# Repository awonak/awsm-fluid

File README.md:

# AWSM - Fluid

> [!NOTE]  
> This project is a work in progress and may contain errors.

3u 12hp Arduino based multi-purpose utility module. 

## Features

**Digital Inputs**

* 2 digital gate/trig inputs
* 2 buttons

**Analog Inputs**

* 4 slide potentiometers w/ addressable LEDs
* 4 CV inputs (-5v to 5v) w/ attenuator pots, summed with each slide pot.

**Analog Outputs**

* 2 PWM 0-10v outputs w/ LED indicator
* Each output paired with additional output which can be an inverted copy (-10v to 0v) or bipolar output (-10v to 10v).

## Concept

This module is meant to be a platform for creating unique utility module scripts using the given inputs and outputs. Some firmware examples are:

* CV controlable ADSR with gate / retrig inputs, envelope curves selected via button, envelope output with EOR/EOF output trigger.
* Clocked burst generator with high gate output during burst sequence.
* Dual LFO w/ shape and rate.
* Random cv generator w/ envelopes.

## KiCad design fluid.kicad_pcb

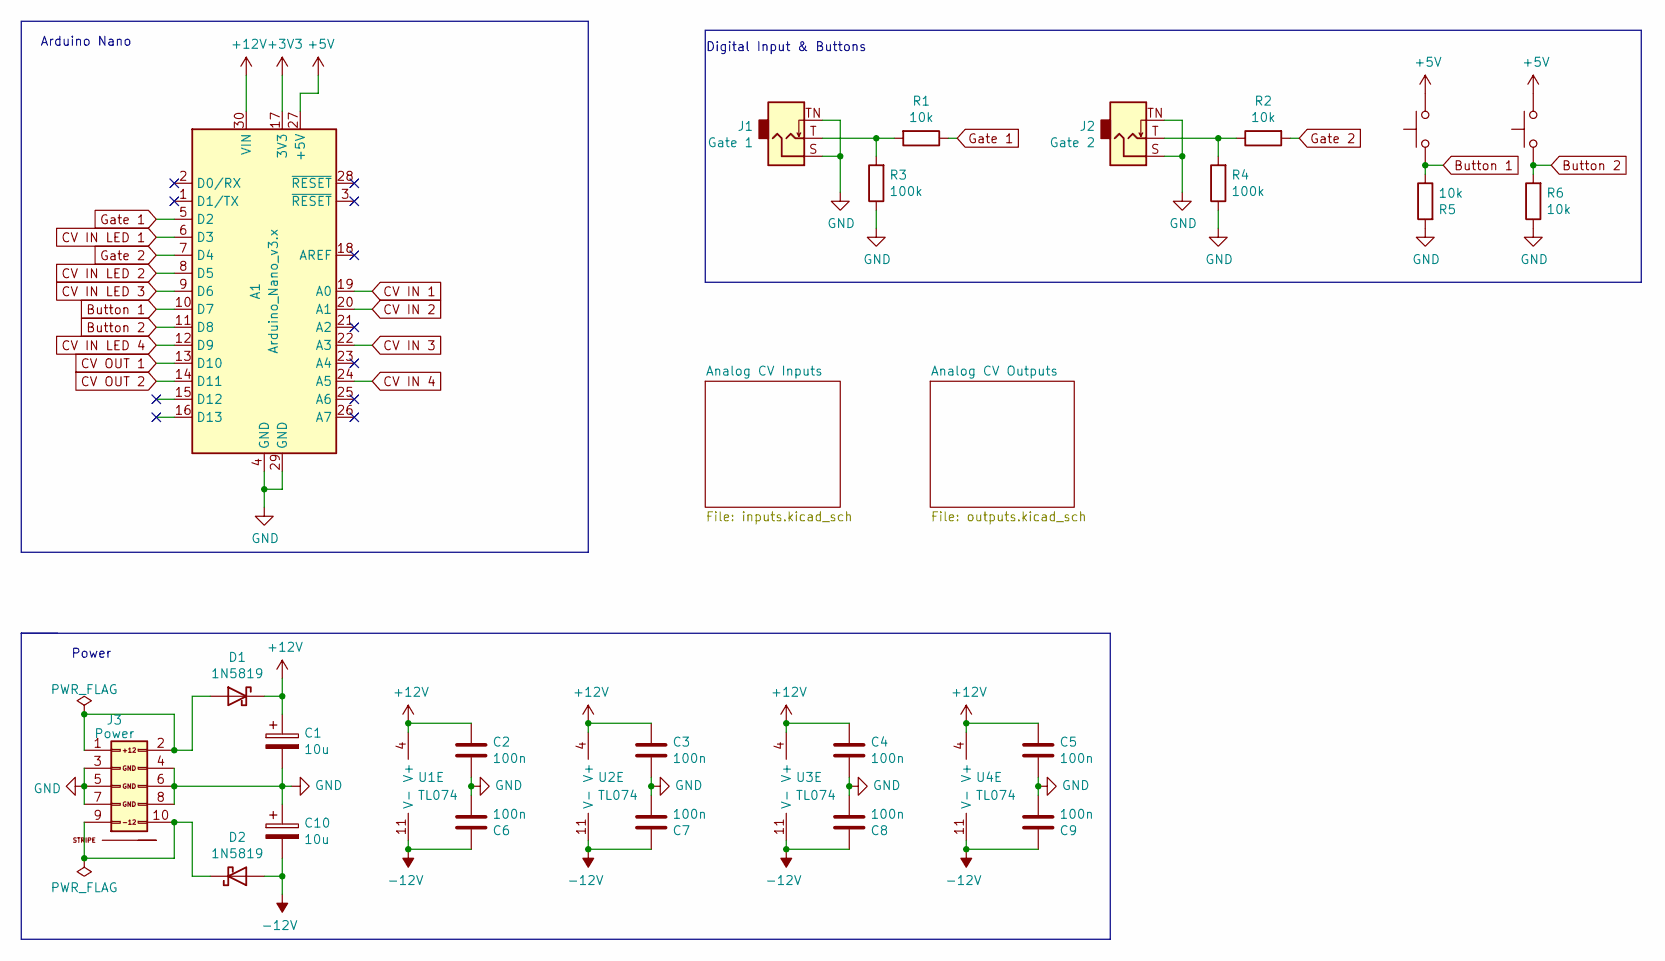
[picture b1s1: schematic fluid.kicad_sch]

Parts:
A1: Arduino_Nano_v3.x; Arduino_Nano
C1, C10: 10u; CP_EIA-3216-18_Kemet-A; LCSC C7171
C2, C3, C4, C5, C6, C7, C8, C9: 100n; C_0402_1005Metric; LCSC C1525
D1, D2: 1N5819; D_SOD-323; LCSC C191023
J1: Gate 1; Jack_3.5mm_QingPu_WQP-PJ398SM_Vertical_CircularHoles_3dModel
J2: Gate 2; Jack_3.5mm_QingPu_WQP-PJ398SM_Vertical_CircularHoles_3dModel
J3: Power; Pins_2x05_2.54mm_TH_EurorackPower
R1, R2, R5, R6: 10k; R_0402_1005Metric; LCSC C25744
R3, R4: 100k; R_0402_1005Metric; LCSC C25741
SW1, SW2: Button; SW_PUSH_6mm
U1, U2, U3, U4: TL074; SOIC-14_3.9x8.7mm_P1.27mm; LCSC C6963

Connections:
+3V3: A1.17 (3V3)
+5V: A1.27 (+5V), SW1.2, SW2.2; also elsewhere on the board
+12V: A1.30 (VIN), C1.1, C2.2, C3.2, C4.2, C5.2, D1.1 (K), U1.4 (V+), U2.4 (V+), U3.4 (V+), U4.4 (V+)
-12V: C6.2, C7.2, C8.2, C9.2, C10.2, D2.2 (A), U1.11 (V-), U2.11 (V-), U3.11 (V-), U4.11 (V-)
Button 1: A1.10 (D7), R5.1, SW1.1
Button 2: A1.11 (D8), R6.2, SW2.1
CV IN 1: A1.19 (A0); also elsewhere on the board
CV IN 2: A1.20 (A1); also elsewhere on the board
CV IN 3: A1.22 (A3); also elsewhere on the board
CV IN 4: A1.24 (A5); also elsewhere on the board
CV IN LED 1: A1.6 (D3); also elsewhere on the board
CV IN LED 2: A1.8 (D5); also elsewhere on the board
CV IN LED 3: A1.9 (D6); also elsewhere on the board
CV IN LED 4: A1.12 (D9); also elsewhere on the board
CV OUT 1: A1.13 (D10); also elsewhere on the board
CV OUT 2: A1.14 (D11); also elsewhere on the board
GND: A1.4 (GND), A1.29 (GND), C1.2, C2.1, C3.1, C4.1, C5.1, C6.1, C7.1, C8.1, C9.1, C10.1, J1.S, J1.TN, J2.S, J2.TN, J3.3 (GND), J3.4 (GND), J3.5 (GND), J3.6 (GND), J3.7 (GND), J3.8 (GND), R3.1, R4.1, R5.2, R6.1; also elsewhere on the board
Gate 1: A1.5 (D2), R1.1
Gate 2: A1.7 (D4), R2.2
unnamed: D1.2 (A), J3.1 (+12V), J3.2 (+12V)
unnamed: D2.1 (K), J3.9 (-12V), J3.10 (-12V)
unnamed: J1.T, R1.2, R3.2
unnamed: J2.T, R2.1, R4.2

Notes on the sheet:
Arduino Nano
Power
Digital Input & Buttons

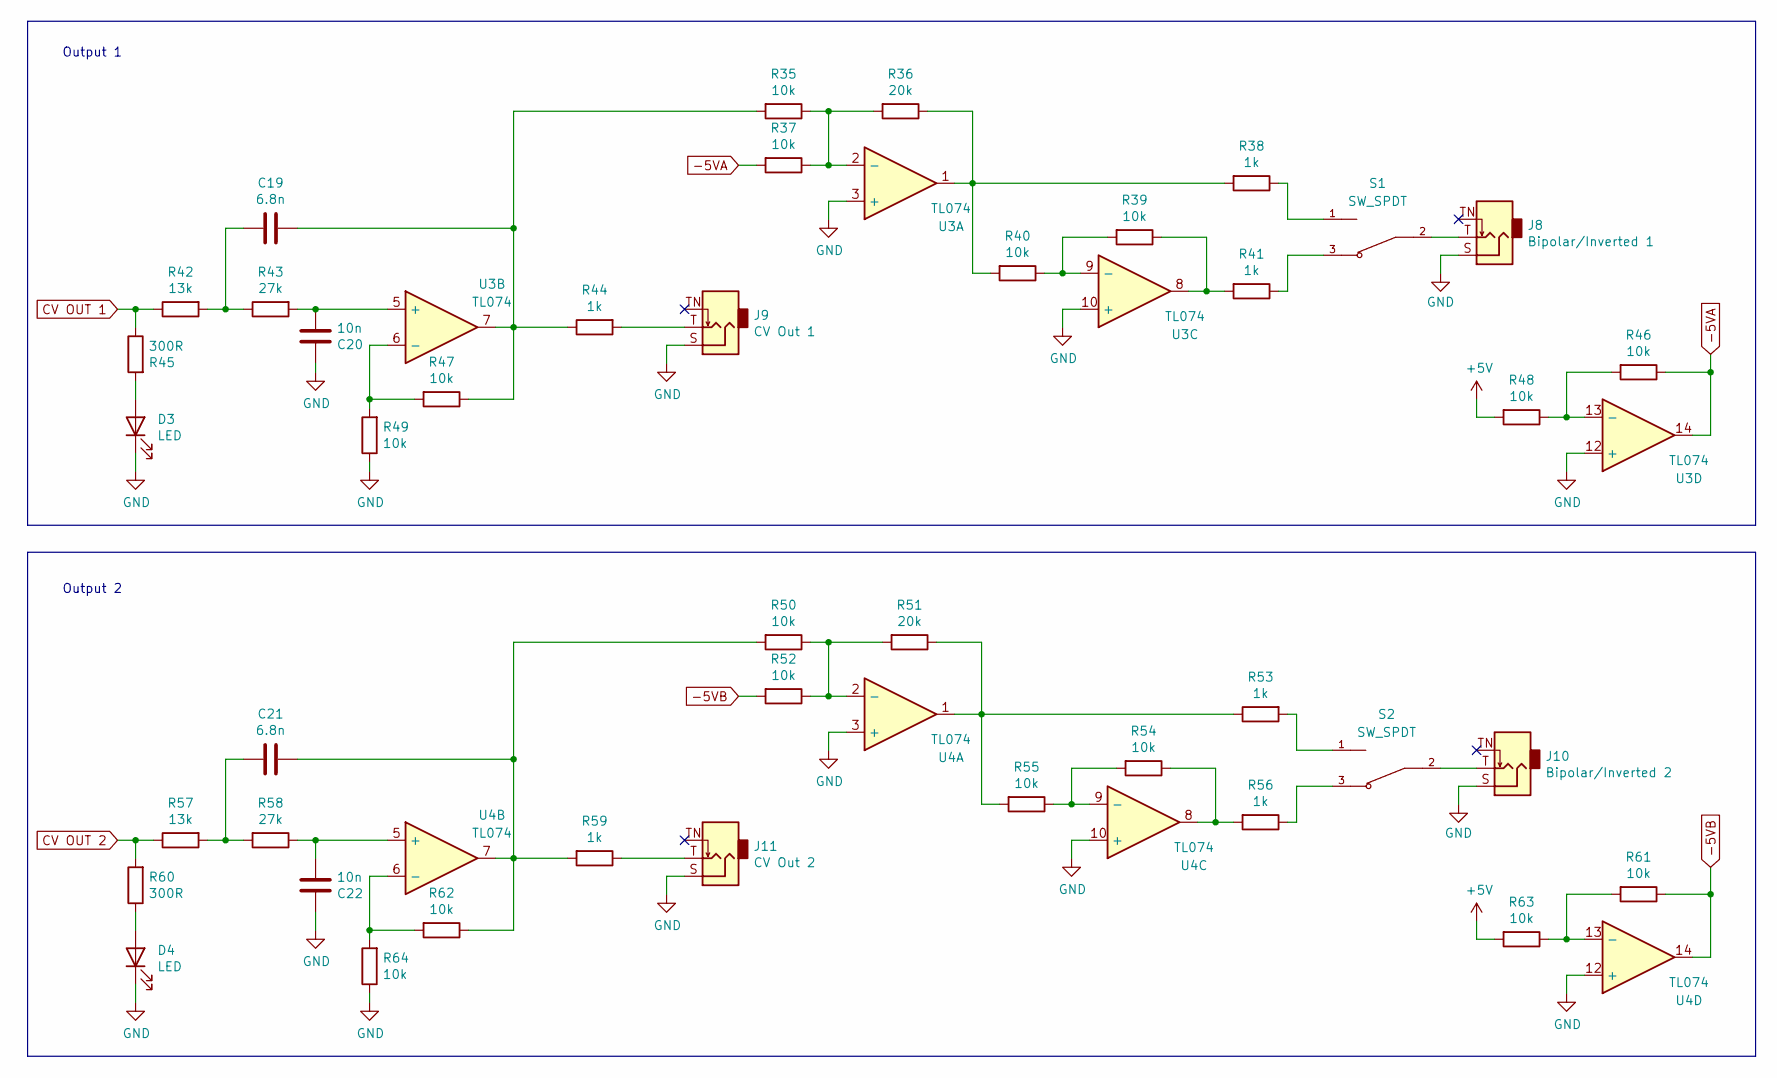
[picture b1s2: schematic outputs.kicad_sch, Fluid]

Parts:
C19, C21: 6.8n; C_0402_1005Metric; LCSC C1542
C20, C22: 10n; C_0402_1005Metric; LCSC C15195
D3, D4: LED; LED_D3.0mm
J8: Bipolar/Inverted 1; Jack_3.5mm_QingPu_WQP-PJ398SM_Vertical_CircularHoles_3dModel
J9: CV Out 1; Jack_3.5mm_QingPu_WQP-PJ398SM_Vertical_CircularHoles_3dModel
J10: Bipolar/Inverted 2; Jack_3.5mm_QingPu_WQP-PJ398SM_Vertical_CircularHoles_3dModel
J11: CV Out 2; Jack_3.5mm_QingPu_WQP-PJ398SM_Vertical_CircularHoles_3dModel
R35, R37, R39, R40, R46, R47, R48, R49, R50, R52, R54, R55, R61, R62, R63, R64: 10k; R_0402_1005Metric; LCSC C25744
R36, R51: 20k; R_0402_1005Metric; LCSC C25765
R38, R41, R44, R53, R56, R59: 1k; R_0402_1005Metric; LCSC C11702
R42, R57: 13k; R_0603_1608Metric; LCSC C22797
R43, R58: 27k; R_0402_1005Metric; LCSC C25771
R45, R60: 300R; R_0402_1005Metric; LCSC C25102
S1, S2: SW_SPDT; SW_2MS1T1B1M2QES
U3, U4: TL074; SOIC-14_3.9x8.7mm_P1.27mm; LCSC C6963

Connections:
+5V: R48.2, R63.2; also elsewhere on the board
-5VA: R37.2, R46.1, U3.14
-5VB: R52.2, R61.1, U4.14
CV OUT 1: R42.1, R45.1; also elsewhere on the board
CV OUT 2: R57.1, R60.2; also elsewhere on the board
GND: C20.2, C22.2, D3.1 (K), D4.1 (K), J8.S, J9.S, J10.S, J11.S, R49.1, R64.1, U3.3 (+), U3.10 (+), U3.12 (+), U4.3 (+), U4.10 (+), U4.12 (+); also elsewhere on the board
unnamed: C19.1, R35.2, R44.1, R47.1, U3.7
unnamed: C19.2, R42.2, R43.1
unnamed: C21.1, R50.2, R59.2, R62.1, U4.7
unnamed: C21.2, R57.2, R58.2
unnamed: D3.2 (A), R45.2
unnamed: D4.2 (A), R60.1
unnamed: J8.T, S1.2
unnamed: J9.T, R44.2
unnamed: J10.T, S2.2
unnamed: J11.T, R59.1
unnamed: R36.1, R38.2, R40.2, U3.1
unnamed: R38.1, S1.1
unnamed: R39.1, R41.2, U3.8
unnamed: R41.1, S1.3
unnamed: R51.1, R53.1, R55.2, U4.1
unnamed: R53.2, S2.1
unnamed: R54.1, R56.2, U4.8
unnamed: R56.1, S2.3
unnamed: R35.1, R36.2, R37.1, U3.2 (-)
unnamed: C20.1, R43.2, U3.5 (+)
unnamed: R47.2, R49.2, U3.6 (-)
unnamed: R39.2, R40.1, U3.9 (-)
unnamed: R46.2, R48.1, U3.13 (-)
unnamed: R50.1, R51.2, R52.1, U4.2 (-)
unnamed: C22.1, R58.1, U4.5 (+)
unnamed: R62.2, R64.2, U4.6 (-)
unnamed: R54.2, R55.1, U4.9 (-)
unnamed: R61.2, R63.1, U4.13 (-)

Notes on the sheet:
Output 2
Output 1

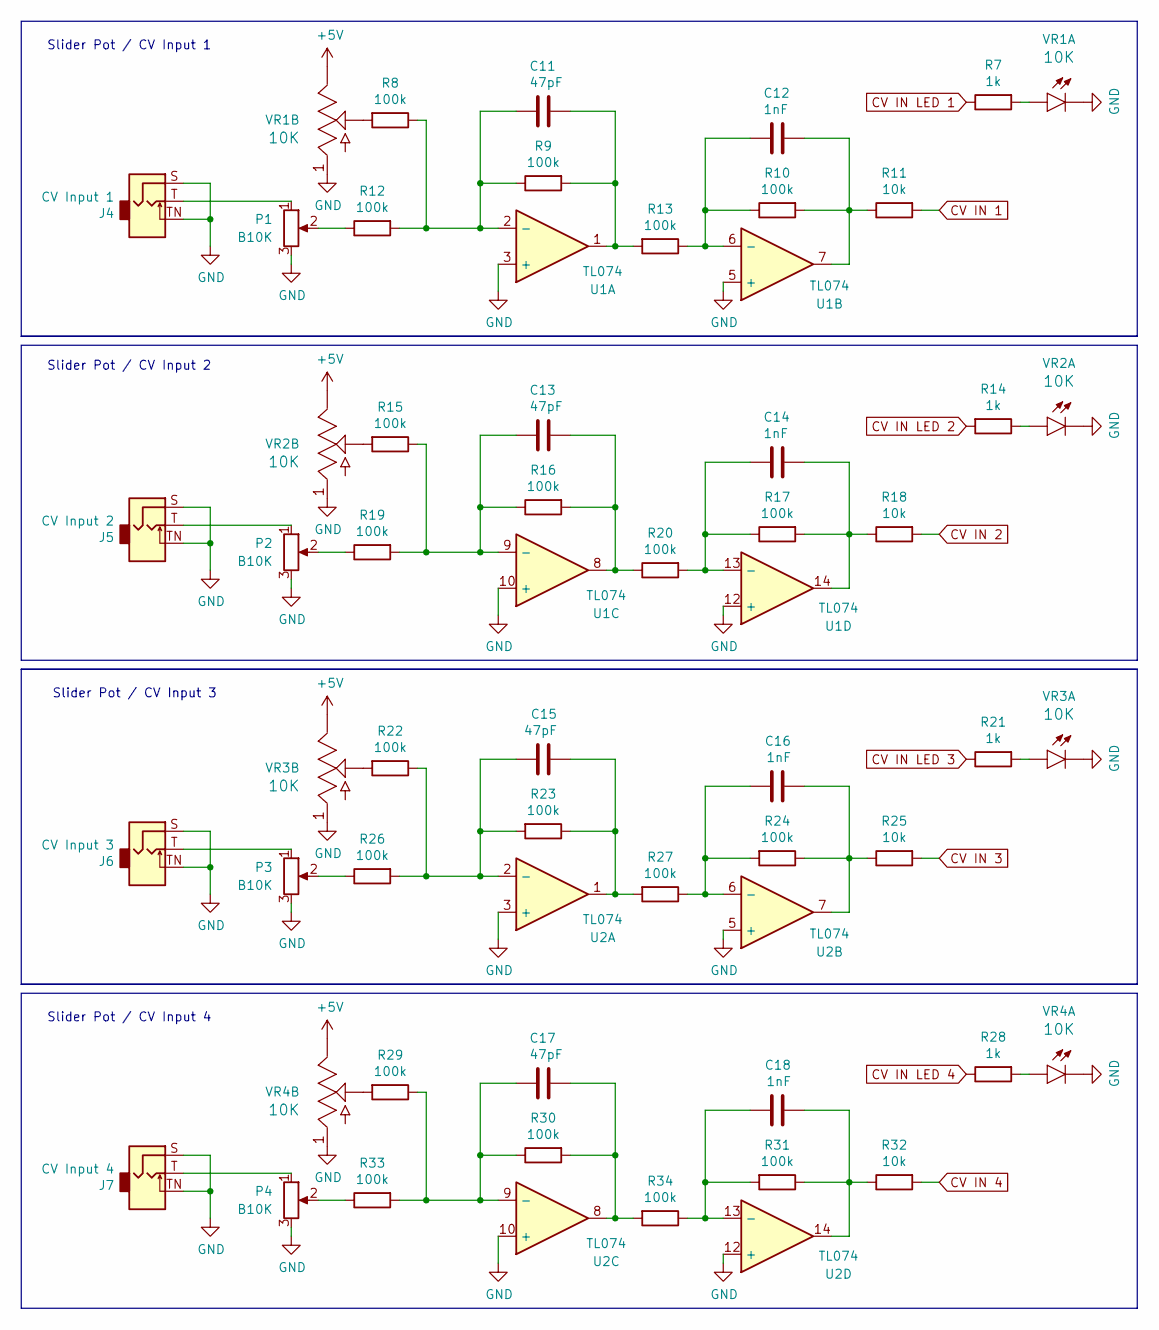
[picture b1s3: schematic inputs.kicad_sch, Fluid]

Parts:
C11, C13, C15, C17: 47pF; C_0402_1005Metric; LCSC C1567
C12, C14, C16, C18: 1nF; C_0402_1005Metric; LCSC C1523
J4: CV Input 1; Jack_3.5mm_QingPu_WQP-PJ398SM_Vertical_CircularHoles_3dModel
J5: CV Input 2; Jack_3.5mm_QingPu_WQP-PJ398SM_Vertical_CircularHoles_3dModel
J6: CV Input 3; Jack_3.5mm_QingPu_WQP-PJ398SM_Vertical_CircularHoles_3dModel
J7: CV Input 4; Jack_3.5mm_QingPu_WQP-PJ398SM_Vertical_CircularHoles_3dModel
P1, P2, P3, P4: B10K; Potentiometer_Alpha_RD901F-40-00D_Single_Vertical
R7, R14, R21, R28: 1k; R_0402_1005Metric; LCSC C11702
R8, R9, R10, R12, R13, R15, R16, R17, R19, R20, R22, R23, R24, R26, R27, R29, R30, R31, R33, R34: 100k; R_0402_1005Metric; LCSC C25741
R11, R18, R25, R32: 10k; R_0402_1005Metric; LCSC C25744
U1, U2: TL074; SOIC-14_3.9x8.7mm_P1.27mm; LCSC C6963
VR1, VR2, VR3, VR4: 10K; Pot_Slider_LED_20mm_RA2045F

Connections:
+5V: VR1.P3 (3), VR2.P3 (3), VR3.P3 (3), VR4.P3 (3); also elsewhere on the board
CV IN 1: R11.2; also elsewhere on the board
CV IN 2: R18.2; also elsewhere on the board
CV IN 3: R25.2; also elsewhere on the board
CV IN 4: R32.2; also elsewhere on the board
CV IN LED 1: R7.1; also elsewhere on the board
CV IN LED 2: R14.2; also elsewhere on the board
CV IN LED 3: R21.1; also elsewhere on the board
CV IN LED 4: R28.1; also elsewhere on the board
GND: J4.S, J4.TN, J5.S, J5.TN, J6.S, J6.TN, J7.S, J7.TN, P1.3, P2.3, P3.3, P4.3, U1.3 (+), U1.5 (+), U1.10 (+), U1.12 (+), U2.3 (+), U2.5 (+), U2.10 (+), U2.12 (+), VR1.LEDC (C), VR1.P1 (1), VR2.LEDC (C), VR2.P1 (1), VR3.LEDC (C), VR3.P1 (1), VR4.LEDC (C), VR4.P1 (1); also elsewhere on the board
unnamed: C11.1, R9.2, R13.2, U1.1
unnamed: C12.1, R10.2, R11.1, U1.7
unnamed: C13.1, R16.2, R20.1, U1.8
unnamed: C14.1, R17.2, R18.1, U1.14
unnamed: C15.2, R23.1, R27.2, U2.1
unnamed: C16.2, R24.1, R25.1, U2.7
unnamed: C17.1, R30.2, R34.2, U2.8
unnamed: C18.2, R31.1, R32.1, U2.14
unnamed: J4.T, P1.1
unnamed: J5.T, P2.1
unnamed: J6.T, P3.1
unnamed: J7.T, P4.1
unnamed: P1.2, R12.1
unnamed: P2.2, R19.1
unnamed: P3.2, R26.1
unnamed: P4.2, R33.1
unnamed: C11.2, R8.1, R9.1, R12.2, U1.2 (-)
unnamed: C12.2, R10.1, R13.1, U1.6 (-)
unnamed: C13.2, R15.1, R16.1, R19.2, U1.9 (-)
unnamed: C14.2, R17.1, R20.2, U1.13 (-)
unnamed: C15.1, R22.1, R23.2, R26.2, U2.2 (-)
unnamed: C16.1, R24.2, R27.1, U2.6 (-)
unnamed: C17.2, R29.1, R30.1, R33.2, U2.9 (-)
unnamed: C18.1, R31.2, R34.1, U2.13 (-)
unnamed: R7.2, VR1.LEDA (A)
unnamed: R8.2, VR1.P2 (2)
unnamed: R14.1, VR2.LEDA (A)
unnamed: R15.2, VR2.P2 (2)
unnamed: R21.2, VR3.LEDA (A)
unnamed: R22.2, VR3.P2 (2)
unnamed: R28.2, VR4.LEDA (A)
unnamed: R29.2, VR4.P2 (2)

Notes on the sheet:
Slider Pot / CV Input 2
Slider Pot / CV Input 4
Slider Pot / CV Input 1
Slider Pot / CV Input 3

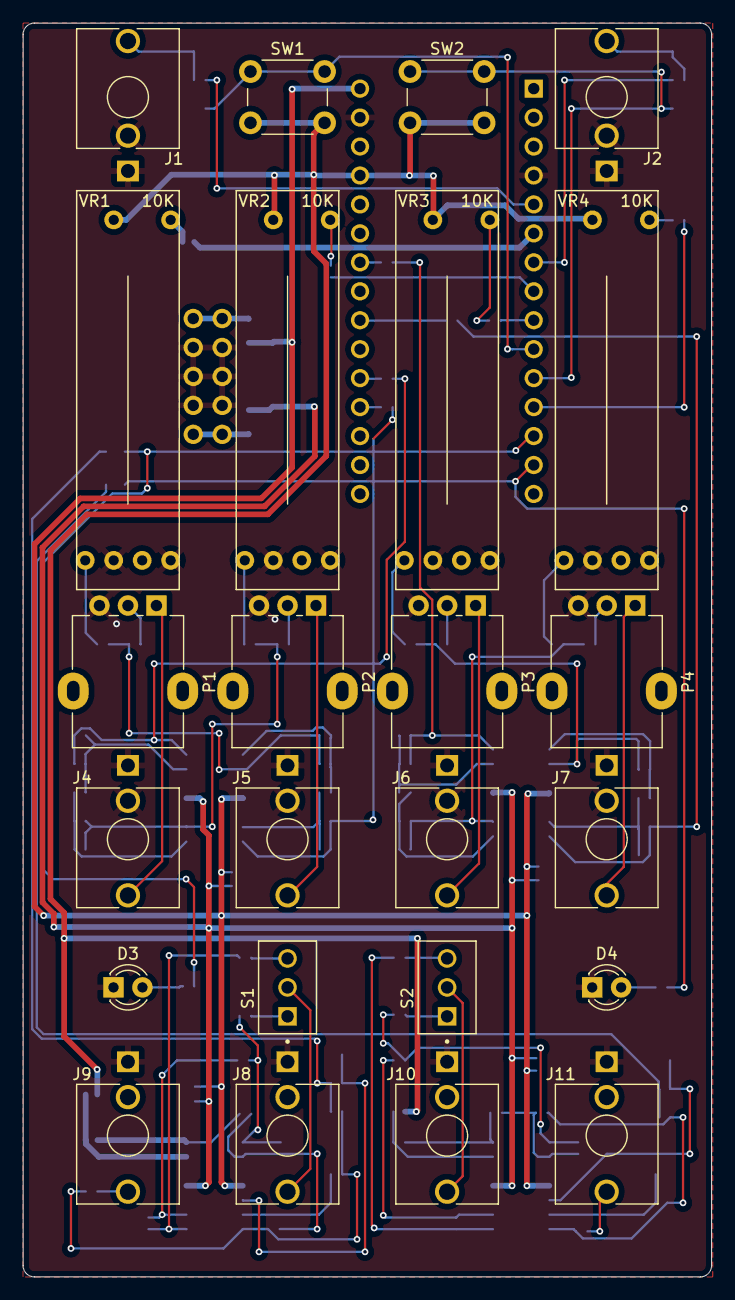
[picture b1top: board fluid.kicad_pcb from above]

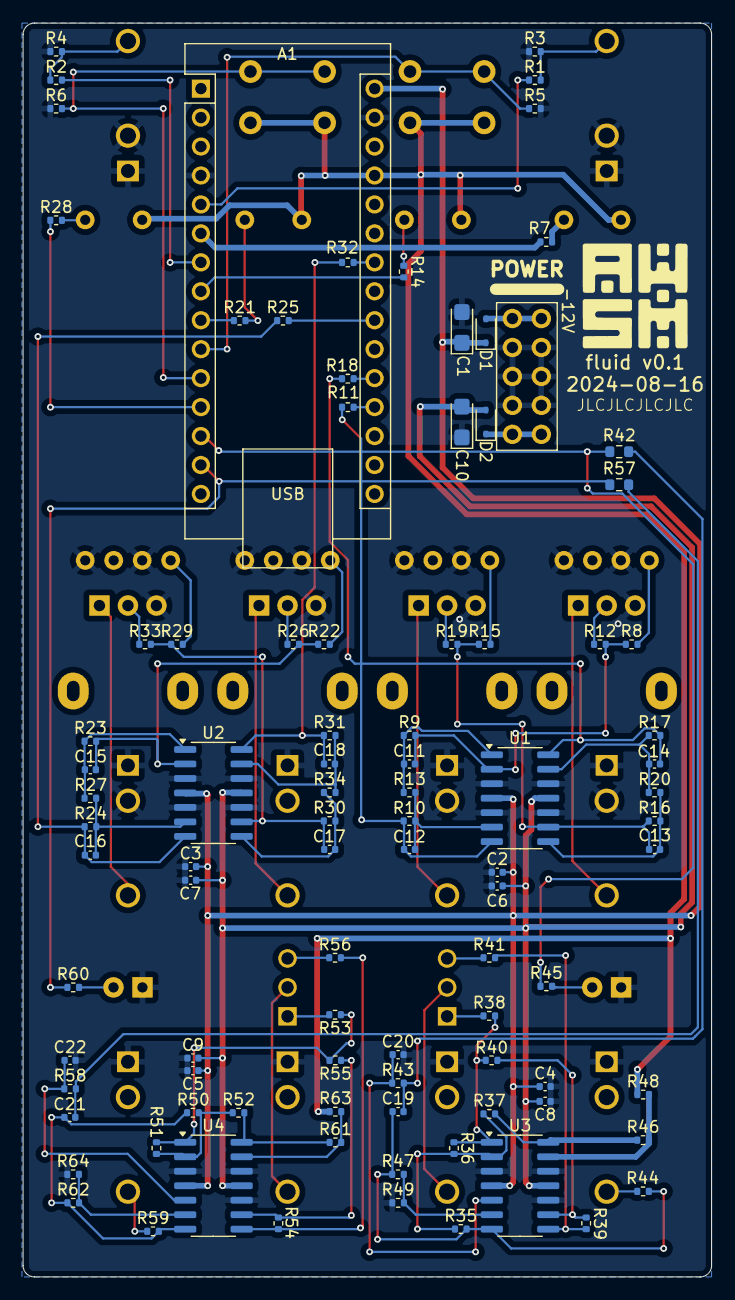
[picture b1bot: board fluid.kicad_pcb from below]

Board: 2 copper layers, 60.4 x 110.0 mm, 118 parts (94 on the bottom side), 84 nets.

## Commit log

2024-08-18 fixed absolute symbol reference. rounded corners of pcb.
2024-08-18 Add README
2024-08-24 Reintroduce the DAC with gain boost from 4.096v to 9.99v. Refactor output LED, increase LED resistor value.
2024-08-24 Add warning about work in progress
2024-08-24 Add cv input range
2024-08-24 update schematic
2024-08-24 reorder annotations, replot pdf schematic
